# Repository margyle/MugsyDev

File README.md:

# Mugsy

This repo has been reset and refactored to contain a monorepo of all Mugsy services. 

🚧**This update is in progress and should not be considered complete at this time.** 🚧

You can find Mugsy's individual repos, CAD files, PCB files, and more at the official Org site on Github:  https://github.com/MugsyOS

## Applications

### Operator
Operator is a FastAPI application designed to manage and control Mugsys hardware devices. All GPIO control is handled by Operator to keep hardware related functionality isolated from the primary DECAF API, allowing for increased hardware compatibility.

Until this monorepo refactor is completed, you can find limited docs, and dev and in progress feature branches on the Org repo: https://github.com/MugsyOS/Operator

### DECAF

DECAF is Mugsy's primary REST API. It handles all the non-hardware related functionality like users, recipes, integrations and tons more. DECAF also manages the brewing process through communications with Operator.

DECAF works with Mugsy's local SQLite database, using [Better-SQLite-3](https://github.com/WiseLibs/better-sqlite3), and [Drizzle](https://orm.drizzle.team/docs/overview) for a comfy dev experience.

### JuneBug

Junebug is Mugsy's React frontend. Written in TypeScript, with some help from [Tailwind](https://tailwindcss.com/), [DaisyUI](https://daisyui.com/), [TanStack Query](https://tanstack.com/query/latest), and [Jotai](https://jotai.org/).

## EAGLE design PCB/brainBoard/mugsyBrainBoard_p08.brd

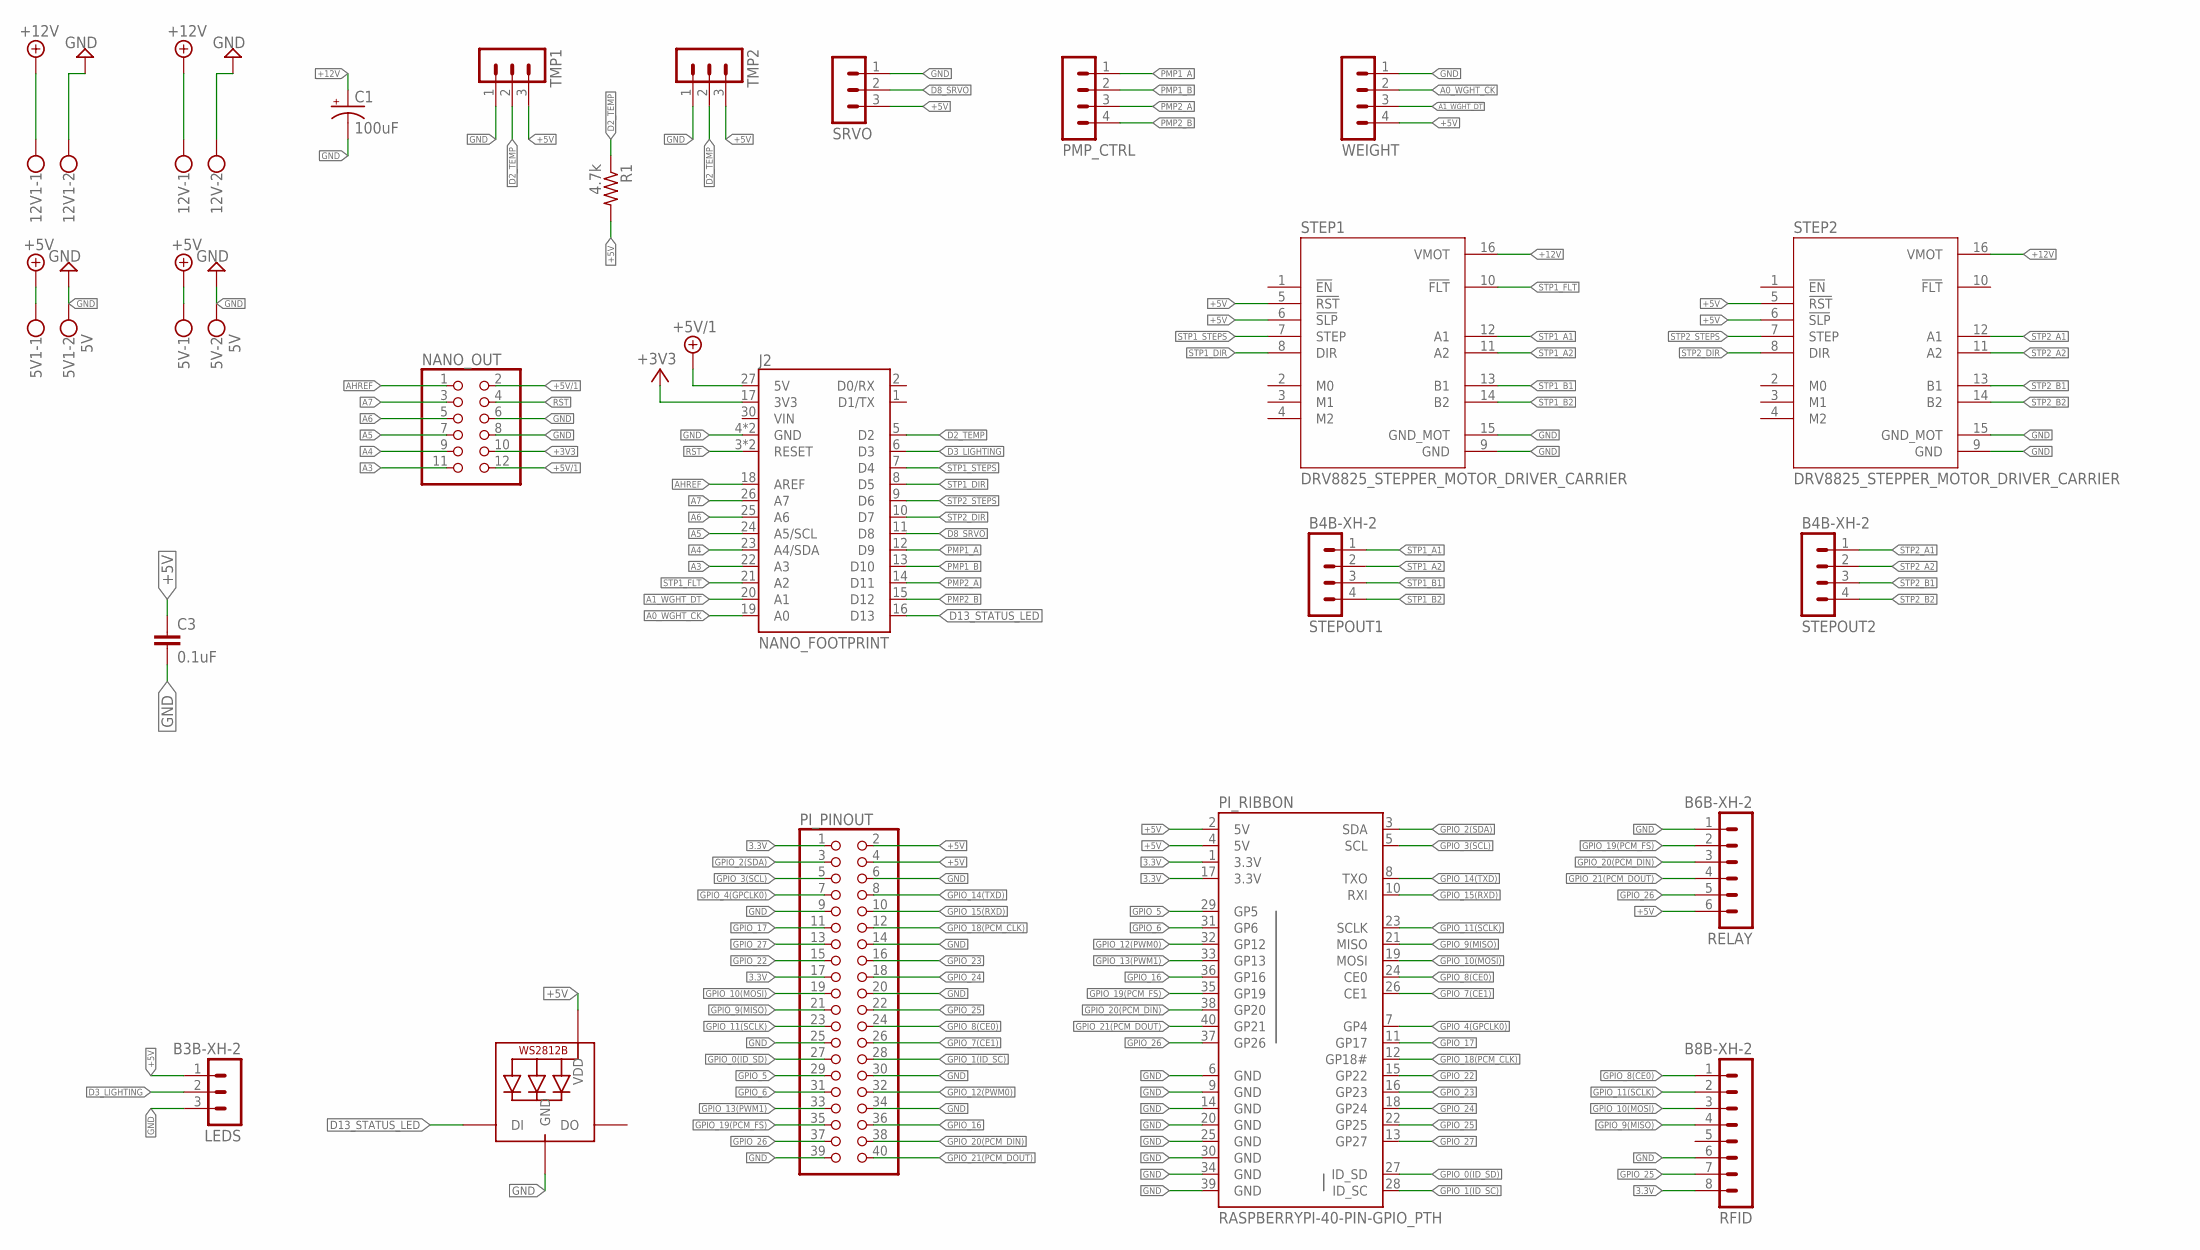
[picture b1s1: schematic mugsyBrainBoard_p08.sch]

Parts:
5V, 5V1: 5V; W237-102
12V, 12V1: W237-102
C1: 100uF; CPOL-RADIAL-2.5MM-6.5MM
C3: 0.1uF; C050-030X075
J2: NANO_FOOTPRINT; NANO
LEDS: B3B-XH-2; B3B-XH-A
NANO_OUT: PINHD-2X6; 2X06
PI_PINOUT: PINHD-2X20; 2X20
PI_RIBBON: RASPBERRYPI-40-PIN-GPIO_PTH; 2X20_SHROUDED
PMP_CTRL: B4B-XH-2; B4B-XH-A
R1: 4.7k; 0207/5V
RELAY: B6B-XH-2; B6B-XH-A
RFID: B8B-XH-2; B8B-XH-A
SRVO: B3B-XH-2; B3B-XH-A
STATUS: WS2812B5050; WS2812B
STEP1, STEP2: DRV8825_STEPPER_MOTOR_DRIVER_CARRIER; IC_DRV8825_STEPPER_MOTOR_DRIVER_CARRIER
STEPOUT1, STEPOUT2: B4B-XH-2; B4B-XH-A
TMP1, TMP2: B3B-XH-2; B3B-XH-A
WEIGHT: B4B-XH-2; B4B-XH-A

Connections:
3.3V: PI_PINOUT.1, PI_PINOUT.17, PI_RIBBON.1 (3.3V), PI_RIBBON.17 (3.3V), RFID.8
+3V3: J2.17 (3V3), NANO_OUT.10
+5V: 5V.1, 5V1.1, C3.1, LEDS.1, PI_PINOUT.2, PI_PINOUT.4, PI_RIBBON.2 (5V), PI_RIBBON.4 (5V), R1.2, RELAY.6, SRVO.3, STATUS.1-VDD (VDD), STEP1.5 (!RST), STEP1.6 (!SLP), STEP2.5 (!RST), STEP2.6 (!SLP), TMP1.3, TMP2.3, WEIGHT.4
+5V/1: J2.27 (5V), NANO_OUT.2, NANO_OUT.12
+12V: 12V.1, 12V1.1, C1.1 (+), STEP1.16 (VMOT), STEP2.16 (VMOT)
A0_WGHT_CK: J2.19 (A0), WEIGHT.2
A1_WGHT_DT: J2.20 (A1), WEIGHT.3
A3: J2.22 (A3), NANO_OUT.11
A4: J2.23 (A4/SDA), NANO_OUT.9
A5: J2.24 (A5/SCL), NANO_OUT.7
A6: J2.25 (A6), NANO_OUT.5
A7: J2.26 (A7), NANO_OUT.3
AHREF: J2.18 (AREF), NANO_OUT.1
D2_TEMP: J2.5 (D2), R1.1, TMP1.2, TMP2.2
D3_LIGHTING: J2.6 (D3), LEDS.2
D8_SRVO: J2.11 (D8), SRVO.2
D13_STATUS_LED: J2.16 (D13), STATUS.4-DIN (DI)
GND: 5V.2, 5V1.2, 12V.2, 12V1.2, C1.2 (-), C3.2, J2.4 (GND), J2.29 (GND), LEDS.3, NANO_OUT.6, NANO_OUT.8, PI_PINOUT.6, PI_PINOUT.9, PI_PINOUT.14, PI_PINOUT.20, PI_PINOUT.25, PI_PINOUT.30, PI_PINOUT.34, PI_PINOUT.39, PI_RIBBON.6 (GND), PI_RIBBON.9 (GND), PI_RIBBON.14 (GND), PI_RIBBON.20 (GND), PI_RIBBON.25 (GND), PI_RIBBON.30 (GND), PI_RIBBON.34 (GND), PI_RIBBON.39 (GND), RELAY.1, RFID.6, SRVO.1, STATUS.3-GND (GND), STEP1.9 (GND), STEP1.15 (GND_MOT), STEP2.9 (GND), STEP2.15 (GND_MOT), TMP1.1, TMP2.1, WEIGHT.1
GPIO_0(ID_SD): PI_PINOUT.27, PI_RIBBON.27 (ID_SD)
GPIO_1(ID_SC): PI_PINOUT.28, PI_RIBBON.28 (ID_SC)
GPIO_2(SDA): PI_PINOUT.3, PI_RIBBON.3 (SDA)
GPIO_3(SCL): PI_PINOUT.5, PI_RIBBON.5 (SCL)
GPIO_4(GPCLK0): PI_PINOUT.7, PI_RIBBON.7 (GP4)
GPIO_5: PI_PINOUT.29, PI_RIBBON.29 (GP5)
GPIO_6: PI_PINOUT.31, PI_RIBBON.31 (GP6)
GPIO_7(CE1): PI_PINOUT.26, PI_RIBBON.26 (CE1)
GPIO_8(CE0): PI_PINOUT.24, PI_RIBBON.24 (CE0), RFID.1
GPIO_9(MISO): PI_PINOUT.21, PI_RIBBON.21 (MISO), RFID.4
GPIO_10(MOSI): PI_PINOUT.19, PI_RIBBON.19 (MOSI), RFID.3
GPIO_11(SCLK): PI_PINOUT.23, PI_RIBBON.23 (SCLK), RFID.2
GPIO_12(PWM0): PI_PINOUT.32, PI_RIBBON.32 (GP12)
GPIO_13(PWM1): PI_PINOUT.33, PI_RIBBON.33 (GP13)
GPIO_14(TXD): PI_PINOUT.8, PI_RIBBON.8 (TXO)
GPIO_15(RXD): PI_PINOUT.10, PI_RIBBON.10 (RXI)
GPIO_16: PI_PINOUT.36, PI_RIBBON.36 (GP16)
GPIO_17: PI_PINOUT.11, PI_RIBBON.11 (GP17)
GPIO_18(PCM_CLK): PI_PINOUT.12, PI_RIBBON.12 (GP18#)
GPIO_19(PCM_FS): PI_PINOUT.35, PI_RIBBON.35 (GP19), RELAY.2
GPIO_20(PCM_DIN): PI_PINOUT.38, PI_RIBBON.38 (GP20), RELAY.3
GPIO_21(PCM_DOUT): PI_PINOUT.40, PI_RIBBON.40 (GP21), RELAY.4
GPIO_22: PI_PINOUT.15, PI_RIBBON.15 (GP22)
GPIO_23: PI_PINOUT.16, PI_RIBBON.16 (GP23)
GPIO_24: PI_PINOUT.18, PI_RIBBON.18 (GP24)
GPIO_25: PI_PINOUT.22, PI_RIBBON.22 (GP25), RFID.7
GPIO_26: PI_PINOUT.37, PI_RIBBON.37 (GP26), RELAY.5
GPIO_27: PI_PINOUT.13, PI_RIBBON.13 (GP27)
PMP1_A: J2.12 (D9), PMP_CTRL.1
PMP1_B: J2.13 (D10), PMP_CTRL.2
PMP2_A: J2.14 (D11), PMP_CTRL.3
PMP2_B: J2.15 (D12), PMP_CTRL.4
RST: J2.3 (RESET), J2.28 (RESET), NANO_OUT.4
STP1_A1: STEP1.12 (A1), STEPOUT1.1
STP1_A2: STEP1.11 (A2), STEPOUT1.2
STP1_B1: STEP1.13 (B1), STEPOUT1.3
STP1_B2: STEP1.14 (B2), STEPOUT1.4
STP1_DIR: J2.8 (D5), STEP1.8 (DIR)
STP1_FLT: J2.21 (A2), STEP1.10 (!FLT)
STP1_STEPS: J2.7 (D4), STEP1.7 (STEP)
STP2_A1: STEP2.12 (A1), STEPOUT2.1
STP2_A2: STEP2.11 (A2), STEPOUT2.2
STP2_B1: STEP2.13 (B1), STEPOUT2.3
STP2_B2: STEP2.14 (B2), STEPOUT2.4
STP2_DIR: J2.10 (D7), STEP2.8 (DIR)
STP2_STEPS: J2.9 (D6), STEP2.7 (STEP)

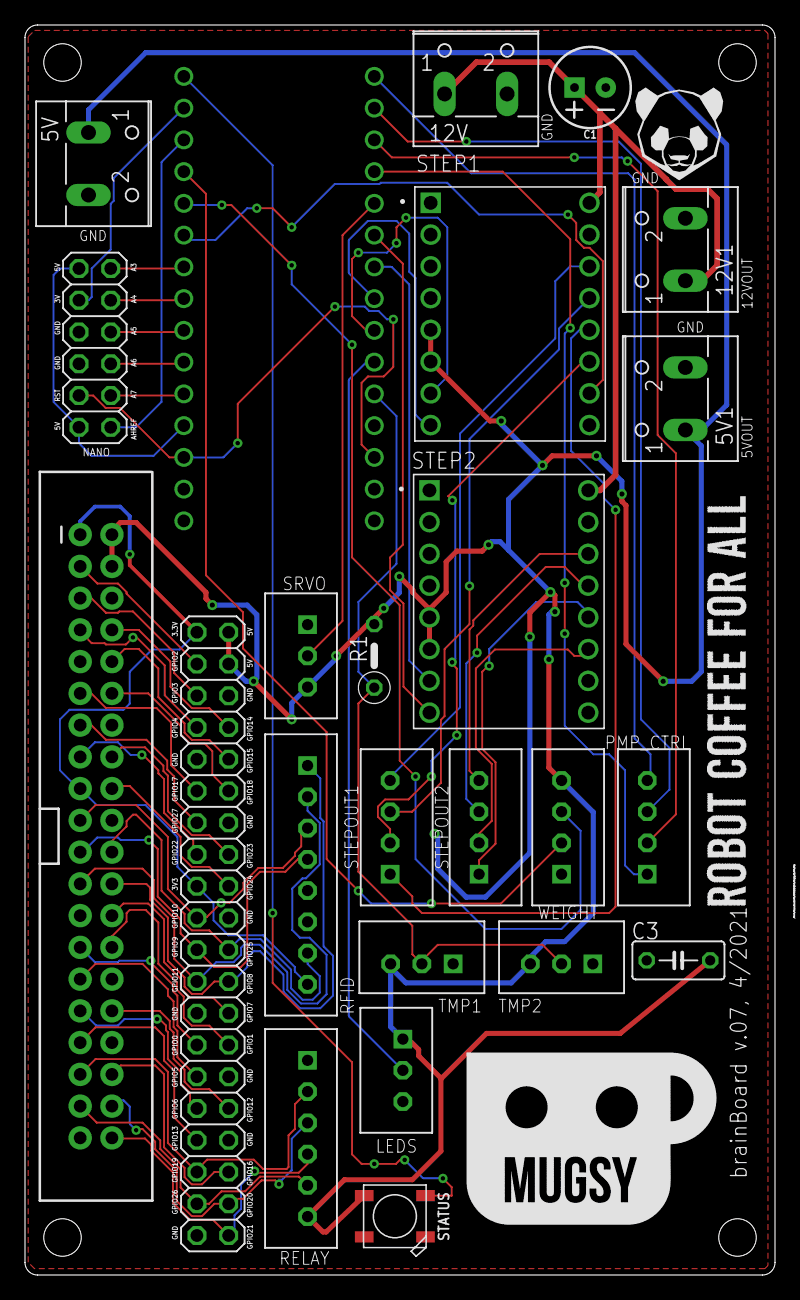
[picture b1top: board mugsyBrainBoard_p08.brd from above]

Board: 2 copper layers, 60.0 x 100.0 mm, 24 parts (0 on the bottom side), 64 nets.

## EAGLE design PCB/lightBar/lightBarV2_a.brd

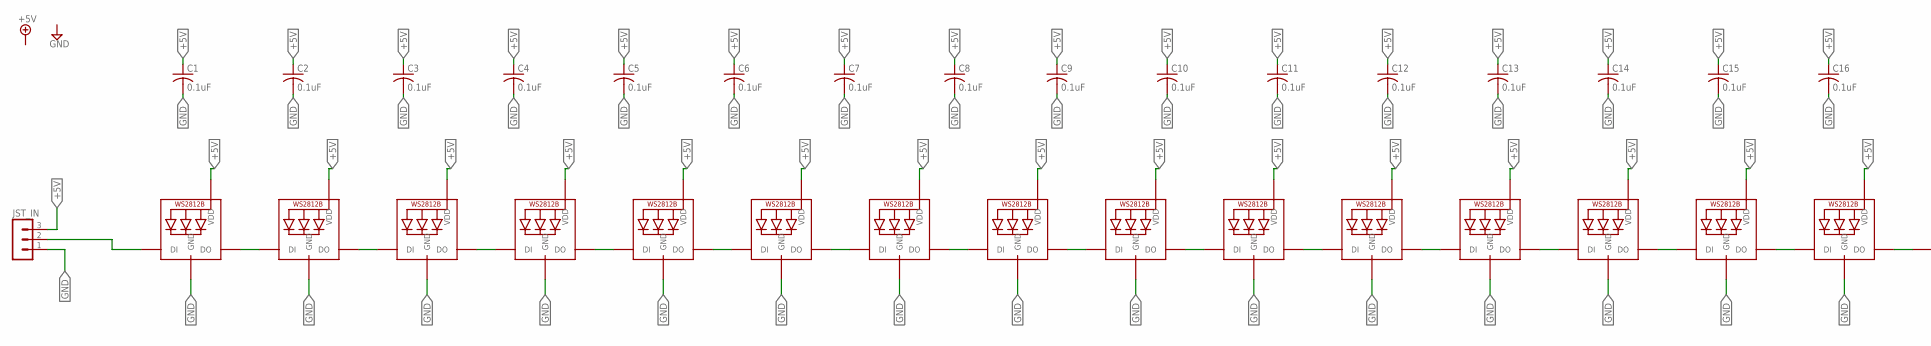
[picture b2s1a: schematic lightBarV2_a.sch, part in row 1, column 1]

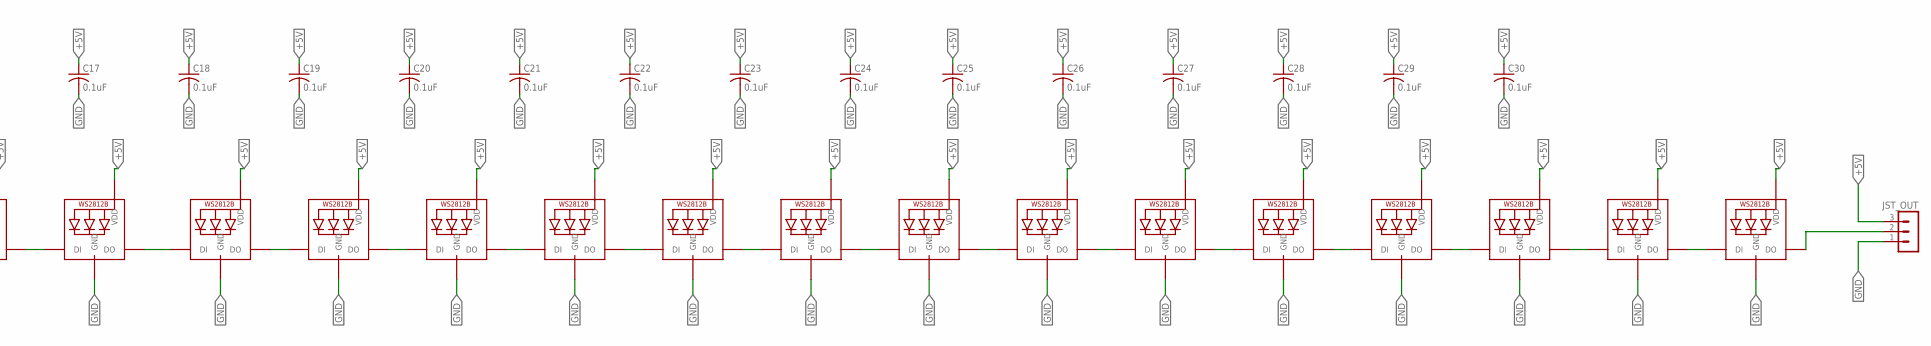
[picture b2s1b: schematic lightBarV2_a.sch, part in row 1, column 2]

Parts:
C1, C2, C3, C4, C5, C6, C7, C8, C9, C10, C11, C12, C13, C14, C15, C16, C17, C18, C19, C20, C21, C22, C23, C24, C25, C26, C27, C28, C29, C30: 0.1uF; C0805K
JST_IN: B3B-XH-2; B3B-XH-A
JST_OUT: B3B-XH-2; B3B-XH-A
LED1, LED2, LED3, LED4, LED5, LED6, LED7, LED8, LED9, LED10, LED11, LED12, LED13, LED14, LED15, LED16, LED17, LED18, LED19, LED20, LED21, LED22, LED23, LED24, LED25, LED26, LED27, LED28, LED29, LED30: WS2812B5050; WS2812B

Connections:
+5V: C1.1, C2.1, C3.1, C4.1, C5.1, C6.1, C7.1, C8.1, C9.1, C10.1, C11.1, C12.1, C13.1, C14.1, C15.1, C16.1, C17.1, C18.1, C19.1, C20.1, C21.1, C22.1, C23.1, C24.1, C25.1, C26.1, C27.1, C28.1, C29.1, C30.1, JST_IN.3, JST_OUT.3, LED1.1-VDD (VDD), LED2.1-VDD (VDD), LED3.1-VDD (VDD), LED4.1-VDD (VDD), LED5.1-VDD (VDD), LED6.1-VDD (VDD), LED7.1-VDD (VDD), LED8.1-VDD (VDD), LED9.1-VDD (VDD), LED10.1-VDD (VDD), LED11.1-VDD (VDD), LED12.1-VDD (VDD), LED13.1-VDD (VDD), LED14.1-VDD (VDD), LED15.1-VDD (VDD), LED16.1-VDD (VDD), LED17.1-VDD (VDD), LED18.1-VDD (VDD), LED19.1-VDD (VDD), LED20.1-VDD (VDD), LED21.1-VDD (VDD), LED22.1-VDD (VDD), LED23.1-VDD (VDD), LED24.1-VDD (VDD), LED25.1-VDD (VDD), LED26.1-VDD (VDD), LED27.1-VDD (VDD), LED28.1-VDD (VDD), LED29.1-VDD (VDD), LED30.1-VDD (VDD)
GND: C1.2, C2.2, C3.2, C4.2, C5.2, C6.2, C7.2, C8.2, C9.2, C10.2, C11.2, C12.2, C13.2, C14.2, C15.2, C16.2, C17.2, C18.2, C19.2, C20.2, C21.2, C22.2, C23.2, C24.2, C25.2, C26.2, C27.2, C28.2, C29.2, C30.2, JST_IN.1, JST_OUT.1, LED1.3-GND (GND), LED2.3-GND (GND), LED3.3-GND (GND), LED4.3-GND (GND), LED5.3-GND (GND), LED6.3-GND (GND), LED7.3-GND (GND), LED8.3-GND (GND), LED9.3-GND (GND), LED10.3-GND (GND), LED11.3-GND (GND), LED12.3-GND (GND), LED13.3-GND (GND), LED14.3-GND (GND), LED15.3-GND (GND), LED16.3-GND (GND), LED17.3-GND (GND), LED18.3-GND (GND), LED19.3-GND (GND), LED20.3-GND (GND), LED21.3-GND (GND), LED22.3-GND (GND), LED23.3-GND (GND), LED24.3-GND (GND), LED25.3-GND (GND), LED26.3-GND (GND), LED27.3-GND (GND), LED28.3-GND (GND), LED29.3-GND (GND), LED30.3-GND (GND)
unnamed: LED29.2-DOUT (DO), LED30.4-DIN (DI)
unnamed: LED28.2-DOUT (DO), LED29.4-DIN (DI)
unnamed: LED27.2-DOUT (DO), LED28.4-DIN (DI)
unnamed: LED26.2-DOUT (DO), LED27.4-DIN (DI)
unnamed: LED25.2-DOUT (DO), LED26.4-DIN (DI)
unnamed: LED24.2-DOUT (DO), LED25.4-DIN (DI)
unnamed: LED23.2-DOUT (DO), LED24.4-DIN (DI)
unnamed: LED22.2-DOUT (DO), LED23.4-DIN (DI)
unnamed: LED21.2-DOUT (DO), LED22.4-DIN (DI)
unnamed: LED20.2-DOUT (DO), LED21.4-DIN (DI)
unnamed: LED19.2-DOUT (DO), LED20.4-DIN (DI)
unnamed: LED18.2-DOUT (DO), LED19.4-DIN (DI)
unnamed: LED17.2-DOUT (DO), LED18.4-DIN (DI)
unnamed: LED16.2-DOUT (DO), LED17.4-DIN (DI)
unnamed: LED15.2-DOUT (DO), LED16.4-DIN (DI)
unnamed: LED14.2-DOUT (DO), LED15.4-DIN (DI)
unnamed: LED13.2-DOUT (DO), LED14.4-DIN (DI)
unnamed: LED12.2-DOUT (DO), LED13.4-DIN (DI)
unnamed: LED11.2-DOUT (DO), LED12.4-DIN (DI)
unnamed: LED10.2-DOUT (DO), LED11.4-DIN (DI)
unnamed: LED9.2-DOUT (DO), LED10.4-DIN (DI)
unnamed: LED8.2-DOUT (DO), LED9.4-DIN (DI)
unnamed: LED7.2-DOUT (DO), LED8.4-DIN (DI)
unnamed: LED6.2-DOUT (DO), LED7.4-DIN (DI)
unnamed: LED5.2-DOUT (DO), LED6.4-DIN (DI)
unnamed: LED4.2-DOUT (DO), LED5.4-DIN (DI)
unnamed: LED3.2-DOUT (DO), LED4.4-DIN (DI)
unnamed: LED1.2-DOUT (DO), LED2.4-DIN (DI)
unnamed: LED2.2-DOUT (DO), LED3.4-DIN (DI)
unnamed: JST_IN.2, LED1.4-DIN (DI)
unnamed: JST_OUT.2, LED30.2-DOUT (DO)

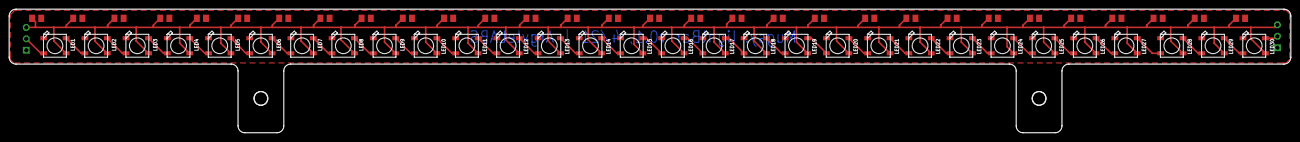
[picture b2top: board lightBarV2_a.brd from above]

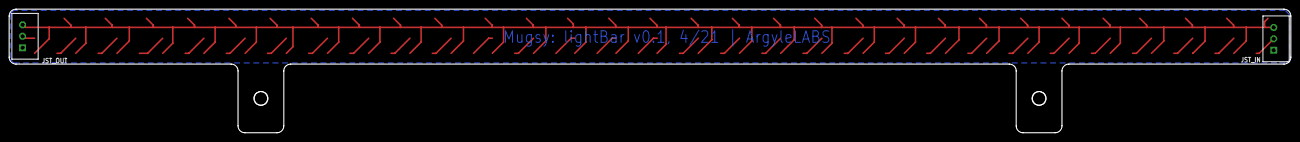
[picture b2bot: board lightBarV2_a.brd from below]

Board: 2 copper layers, 280.0 x 27.0 mm, 62 parts (2 on the bottom side), 33 nets.

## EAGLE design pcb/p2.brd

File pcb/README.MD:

##Early proto for the V2 mainboard.

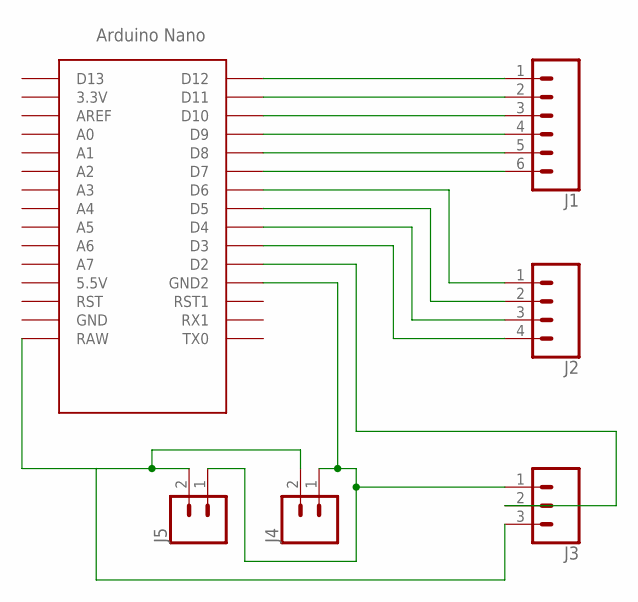
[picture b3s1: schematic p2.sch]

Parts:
J1: CONN_06LONGPADS; 1X06_LONGPADS
J2: CONN_04LONGPADS; 1X04_LONGPADS
J3: CONN_03LONGPADS; 1X03_LONGPADS
J4, J5: CONN_02PTH3; 1X02_LONGPADS
U$1: NANO

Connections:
unnamed: J1.1, U$1.D12
unnamed: J1.2, U$1.D11
unnamed: J1.3, U$1.D10
unnamed: J1.4, U$1.D9
unnamed: J1.5, U$1.D8
unnamed: J1.6, U$1.D7
unnamed: J2.1, U$1.D6
unnamed: J2.2, U$1.D5
unnamed: J2.3, U$1.D4
unnamed: J2.4, U$1.D3
unnamed: J3.2, U$1.D2
unnamed: J3.3, J4.2, J5.2, U$1.RAW
unnamed: J3.1, J4.1, J5.1, U$1.GND1 (GND2)

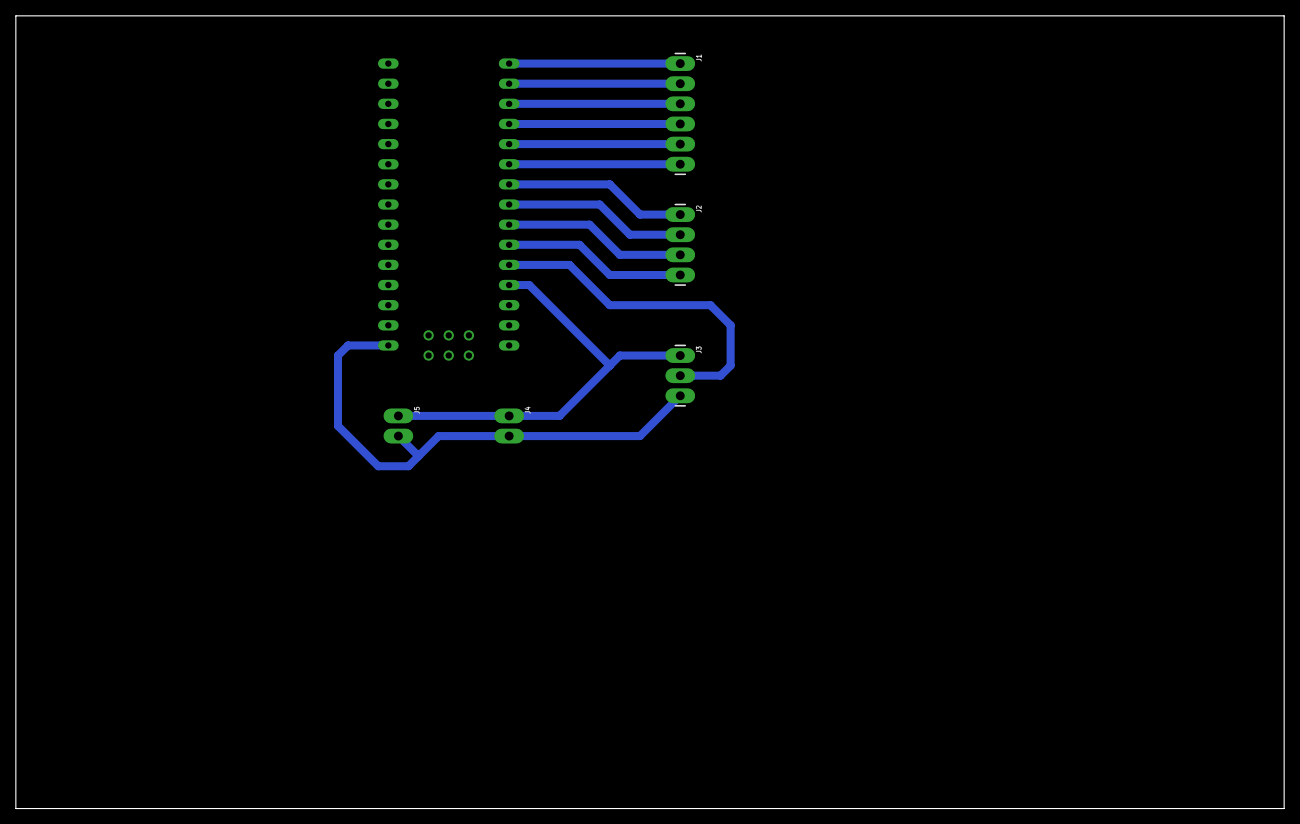
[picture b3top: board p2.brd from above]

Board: 2 copper layers, 160.0 x 100.0 mm, 6 parts (0 on the bottom side), 13 nets.

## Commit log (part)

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2018-03-19 Initial Cad Upload
2018-05-15 Creating DB directory
2018-05-15 Initial commit for dev DB
    Available in SQL and XML
2018-05-15 initial dev DB commit
2018-06-16 QA commit, docs to follow
2018-06-16 Ino zip commit
    Ino provides CLI Arduino control over USB/Serial
2018-06-16 relayContol.py commit
    relayContol.py is a basic testing script to run through Mugsy's relay breakout board.
2018-06-23 Create pinRelayTester.ino
    Basic digital pin tester
    Wiring: Connect digital pin 12 to the S pin on relay
    Connect 3V3 pin to + pin on relay
    Connect GND pin to - pin on relay
2018-08-11 initial commit
    First test of a stacking controller/breakout mounting plate. Individual plates will be separated by m3 stand offs.
2018-08-11 Add files via upload
    Added footprints for Pi, L2989 Module, 4x Relay Module
2018-08-14 Add files via upload
    RGB LED Mount for 15mm Extrusion
2018-08-25 Add files via upload
    Secures touchscreen to front acrylic panel.
2018-08-25 Add files via upload
    Updated hole placement.
2018-09-24 STL Updates
    Final controller plate version: Redesigned to be much more basic, now able to be laser cut in addition to 3d printable
    Initial update of Pour Over Mechanism Mid Section for V3 set up.
2018-09-27 Pour over mechanism lid(laser cut)
2018-10-17 initial commit
    Status: Working. This script reads the boiler temperature, converts that value to an RGB value,
    sends it to the LEDs and then sends the temp over serial to the Pi
    TODO Need to add comments, clean up old pattern references and any other left over code from base file
    This code is just a hacked version of the FastLED DemoReel100 by Mark Kriegsman.
2018-10-18 Initial Commit
    I am maos.
    Status: Working. This script scans for an RFID tag and sends the resulting key over serial to the pi
    Built on top of RFID reader code by Aritro Mukherjee from https://www.hackster.io/Aritro
2018-11-09 More STL uploads
2018-11-21 Add files via upload
    controllerPlatesLaser.dxf Laser file for controller plates
    behindScreenDividerLaser.dxf Laser file for the divider which separates the screen electronics from the coffee making bits.
2018-12-04 Create mugReader
2018-12-04 Rename config.py to decafConfig.py
2018-12-05 added barcode scanner resource endpoint
2019-01-20 Grinder spout and mount upload
2019-01-26 Create coneStepperSerialControl.ino
    //need to switch AccelStepper lib as well as integrate into the larger runtime.
    //200 steps = one rotation of stepper, 1600 steps = one rotation of pour over cone
    //commands can be chained
    //format = <CW,1600,60.00> (Direction, Steps, Speed)
    //Chained example: <CW,800,60.00><CC,800,60.00><CW,800,60.00><CC,1600,60.00><CW,1600,60.00>
2019-02-14 Add files via upload
    New internal plug cap to protect contacts.
2019-03-21 Mag Connector Upload
2019-03-29 Add files via upload
    V4 Panel Mount
2019-04-23 interface image upload
2019-04-24 flat files for helper statuses
2019-05-22 Cloud Control API Endpoints
    Need to convert these over to Flask.
2019-05-22 Create coffeeNowCloud.php
    Need to add back in Auth and Logging
2019-05-23 add key detective
2019-05-23 added key detective
2019-06-07 Create LICENSE
2019-06-14 Fixed Seria Command Chaining
2019-06-15 added additional command for relay control
2019-06-22 Create mugsyCommander.ino
    Need to add back water timings and dual4 temp sensors
2019-06-22 updated inc directory
2019-07-15 Add files via upload
    Almost complete CAD model for entire Mugsy. Still need to add remaining electronics, boiler, grinder and hopper as well as link the assemblies properly. 99% of the structural parts are in there thoug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
2019-08-20 Fixed incorrect hole size due to export error
2019-08-20 base side panels for extensions, 210 and 270mm
2019-08-20 Kiosk mode and recipe list css reqs
2019-08-20 Added remaining Mugsy Icons
2019-08-20 Added web and Mugsy Icon font sets
2019-08-31 Create brewing.php
    Need to put timer back in after refactoring. Also need to create a new css class for list items and remove inline css.
2019-09-01 Update brewing.php
    Added the step timer display js back in. Still need to link progress bar to timer and put function in it's own js file.
2019-09-01 Fixed recipeName variable in brew progress header
2019-09-27 Rename interface.sh to mugsyStartUp.sh
2019-10-09 update to cloud control schema
2019-11-11 Adding back in temp sensors
2019-11-11 Add in second temp sensor and return average
2019-11-11 comment clean up
    added comment breaks to simplify editing for new coders
2019-11-12 Updated PID lib
2019-11-13 API key creation
2019-11-13 Create integrations.php
    Need to link revocation button to confirmation and db. Also need to make bootstrap table js a local resource along with moving some inline css.
2019-11-13 Add files via upload
    Need to move custom styles to a custom.css file
2019-11-13 Adding webfonts
2019-11-13 remove "test" option from api type selection
2019-11-28 base recipe builder frame
    Lots to add back in, main js, form types and db conn. Also need to pull inline css.
2019-12-05 update schema for recipeSteps table
2019-12-05 added stickyList and optionEditor Wrapper
2019-12-05 pass dragged element's id to editor
2019-12-05 added option type to editor update logic
2019-12-05 prepping js file for input instead of inline
2019-12-05 add is option set check
2019-12-06 add sliders for spout positioning
2019-12-06 cosine vector similarity for coffee recommendations
2019-12-06 separate file for form holder variables
2019-12-07 add step values to json object
2019-12-07 show grinder settings on launch
2019-12-07 add in time, pause, and report form types
2019-12-07 show step count progress, top right
2019-12-07 strip js and form variables and move to import files
2019-12-07 added in all forms for all step options
2019-12-21 Fixes
2019-12-21 More fixes
2020-01-02 belt route sketch
2020-06-16 Front Panel Rotary Encoder Breakout Mount
2020-06-16 Option mount for barcode scanner servo control
2020-12-04 flexBlock_0.1
2021-05-10 Update to use drv8825 type step motor controller
2021-05-11 Offset mount for LED PCB (enclosure lighting)
2021-05-13 Added stepper enable/disable functionality
2021-05-17 Very minor tweaks to streamline temp testing
2021-05-28 add PCB files for v.08 controller
2021-12-06 Add cup sensor mount stl.
    The cup sensor makes sure Mugsy only brews when a mug is present.
2021-12-23 Rear enclosure lightbar mounts
    These mounts allow you to place the lightbar at the rear of the enclosure when you have a front panel color other than white. It will throw the LED visualizations against the wall behind the unit.
2024-09-22 Reset repository, begin refactor to Mugsy monorepo for all services
2024-09-22 setup: add Operator mainline into Mugsy monorepo
2024-09-22 setup: update readme and gitignore
2024-09-22 setup: add monorepo readme, revert operator repo
2024-09-22 setup: update ignore to catch Operator subdirectories
2024-09-22 Bump certifi from 2024.2.2 to 2024.7.4 in /Operator
    Bumps [certifi](https://github.com/certifi/python-certifi) from 2024.2.2 to 2024.7.4.
    - [Commits](https://github.com/certifi/python-certifi/compare/2024.02.02...2024.07.04)
    ---
    updated-dependencies:
    - dependency-name: certifi
    dependency-type: direct:production
2024-09-22 Bump urllib3 from 2.2.1 to 2.2.2 in /Operator
    Bumps [urllib3](https://github.com/urllib3/urllib3) from 2.2.1 to 2.2.2.
    - [Release notes](https://github.com/urllib3/urllib3/releases)
    - [Changelog](https://github.com/urllib3/urllib3/blob/main/CHANGES.rst)
    - [Commits](https://github.com/urllib3/urllib3/compare/2.2.1...2.2.2)
    ---
    updated-dependencies:
2024-09-22 Bump cryptography from 42.0.8 to 43.0.1 in /Operator
    Bumps [cryptography](https://github.com/pyca/cryptography) from 42.0.8 to 43.0.1.
    - [Changelog](https://github.com/pyca/cryptography/blob/main/CHANGELOG.rst)
    - [Commits](https://github.com/pyca/cryptography/compare/42.0.8...43.0.1)
    ---
    updated-dependencies:
    - dependency-name: cryptography
2024-09-22 Bump requests from 2.31.0 to 2.32.2 in /Operator
    Bumps [requests](https://github.com/psf/requests) from 2.31.0 to 2.32.2.
    - [Release notes](https://github.com/psf/requests/releases)
    - [Changelog](https://github.com/psf/requests/blob/main/HISTORY.md)
    - [Commits](https://github.com/psf/requests/compare/v2.31.0...v2.32.2)
    ---
    updated-dependencies:
2024-10-15 Bump starlette from 0.37.2 to 0.40.0 in /Operator
    Bumps [starlette](https://github.com/encode/starlette) from 0.37.2 to 0.40.0.
    - [Release notes](https://github.com/encode/starlette/releases)
    - [Changelog](https://github.com/encode/starlette/blob/master/docs/release-notes.md)
    - [Commits](https://github.com/encode/starlette/compare/0.37.2...0.40.0)
    ---
    updated-dependencies:
2025-02-11 Bump cryptography from 42.0.8 to 44.0.1 in /Operator
    Bumps [cryptography](https://github.com/pyca/cryptography) from 42.0.8 to 44.0.1.
    - [Changelog](https://github.com/pyca/cryptography/blob/main/CHANGELOG.rst)
    - [Commits](https://github.com/pyca/cryptography/compare/42.0.8...44.0.1)
    ---
    updated-dependencies:
    - dependency-name: cryptography
2025-04-24 Bump h11 from 0.14.0 to 0.16.0 in /Operator
    Bumps [h11](https://github.com/python-hyper/h11) from 0.14.0 to 0.16.0.
    - [Commits](https://github.com/python-hyper/h11/compare/v0.14.0...v0.16.0)
    ---
    updated-dependencies:
    - dependency-name: h11
    dependency-version: 0.16.0
2025-06-10 Bump requests from 2.31.0 to 2.32.4 in /Operator
    Bumps [requests](https://github.com/psf/requests) from 2.31.0 to 2.32.4.
    - [Release notes](https://github.com/psf/requests/releases)
    - [Changelog](https://github.com/psf/requests/blob/main/HISTORY.md)
    - [Commits](https://github.com/psf/requests/compare/v2.31.0...v2.32.4)
    ---
    updated-dependencies:
2025-06-19 Bump urllib3 from 2.2.1 to 2.5.0 in /Operator
    Bumps [urllib3](https://github.com/urllib3/urllib3) from 2.2.1 to 2.5.0.
    - [Release notes](https://github.com/urllib3/urllib3/releases)
    - [Changelog](https://github.com/urllib3/urllib3/blob/main/CHANGES.rst)
    - [Commits](https://github.com/urllib3/urllib3/compare/2.2.1...2.5.0)
    ---
    updated-dependencies:
2025-09-22 Bump authlib from 1.3.1 to 1.6.4 in /Operator
    Bumps [authlib](https://github.com/authlib/authlib) from 1.3.1 to 1.6.4.
    - [Release notes](https://github.com/authlib/authlib/releases)
    - [Changelog](https://github.com/authlib/authlib/blob/main/docs/changelog.rst)
    - [Commits](https://github.com/authlib/authlib/compare/v1.3.1...v1.6.4)
    ---
    updated-dependencies:
2025-10-10 Bump authlib from 1.3.1 to 1.6.5 in /Operator
    Bumps [authlib](https://github.com/authlib/authlib) from 1.3.1 to 1.6.5.
    - [Release notes](https://github.com/authlib/authlib/releases)
    - [Changelog](https://github.com/authlib/authlib/blob/main/docs/changelog.rst)
    - [Commits](https://github.com/authlib/authlib/compare/v1.3.1...v1.6.5)
    ---
    updated-dependencies:
2025-10-28 Bump starlette from 0.40.0 to 0.49.1 in /Operator
    Bumps [starlette](https://github.com/Kludex/starlette) from 0.40.0 to 0.49.1.
    - [Release notes](https://github.com/Kludex/starlette/releases)
    - [Changelog](https://github.com/Kludex/starlette/blob/main/docs/release-notes.md)
    - [Commits](https://github.com/Kludex/starlette/compare/0.40.0...0.49.1)
    ---
    updated-dependencies:
2025-12-06 Bump urllib3 from 2.2.1 to 2.6.0 in /Operator
    Bumps [urllib3](https://github.com/urllib3/urllib3) from 2.2.1 to 2.6.0.
    - [Release notes](https://github.com/urllib3/urllib3/releases)
    - [Changelog](https://github.com/urllib3/urllib3/blob/main/CHANGES.rst)
    - [Commits](https://github.com/urllib3/urllib3/compare/2.2.1...2.6.0)
    ---
    updated-dependencies:
2026-01-08 Bump urllib3 from 2.2.1 to 2.6.3 in /Operator
    Bumps [urllib3](https://github.com/urllib3/urllib3) from 2.2.1 to 2.6.3.
    - [Release notes](https://github.com/urllib3/urllib3/releases)
    - [Changelog](https://github.com/urllib3/urllib3/blob/main/CHANGES.rst)
    - [Commits](https://github.com/urllib3/urllib3/compare/2.2.1...2.6.3)
    ---
    updated-dependencies:

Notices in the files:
parts and their libraries:
SparkFun-Connectors: Licensing: Creative Commons ShareAlike 4.0 International - https://creativecommons.org/licenses/by-sa/4.0
